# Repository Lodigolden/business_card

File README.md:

# Business Card

## Overview
I saw the idea for a PCB business card online, but for the most part the PCBs didn't actually do anything. I saw a fun opportunity to give anyone who's got the card a clock/thermometer that they might get some use out of.

## Use

## Build Your Own!
See the Bill of Materials (BoM) in the docs/ folder.

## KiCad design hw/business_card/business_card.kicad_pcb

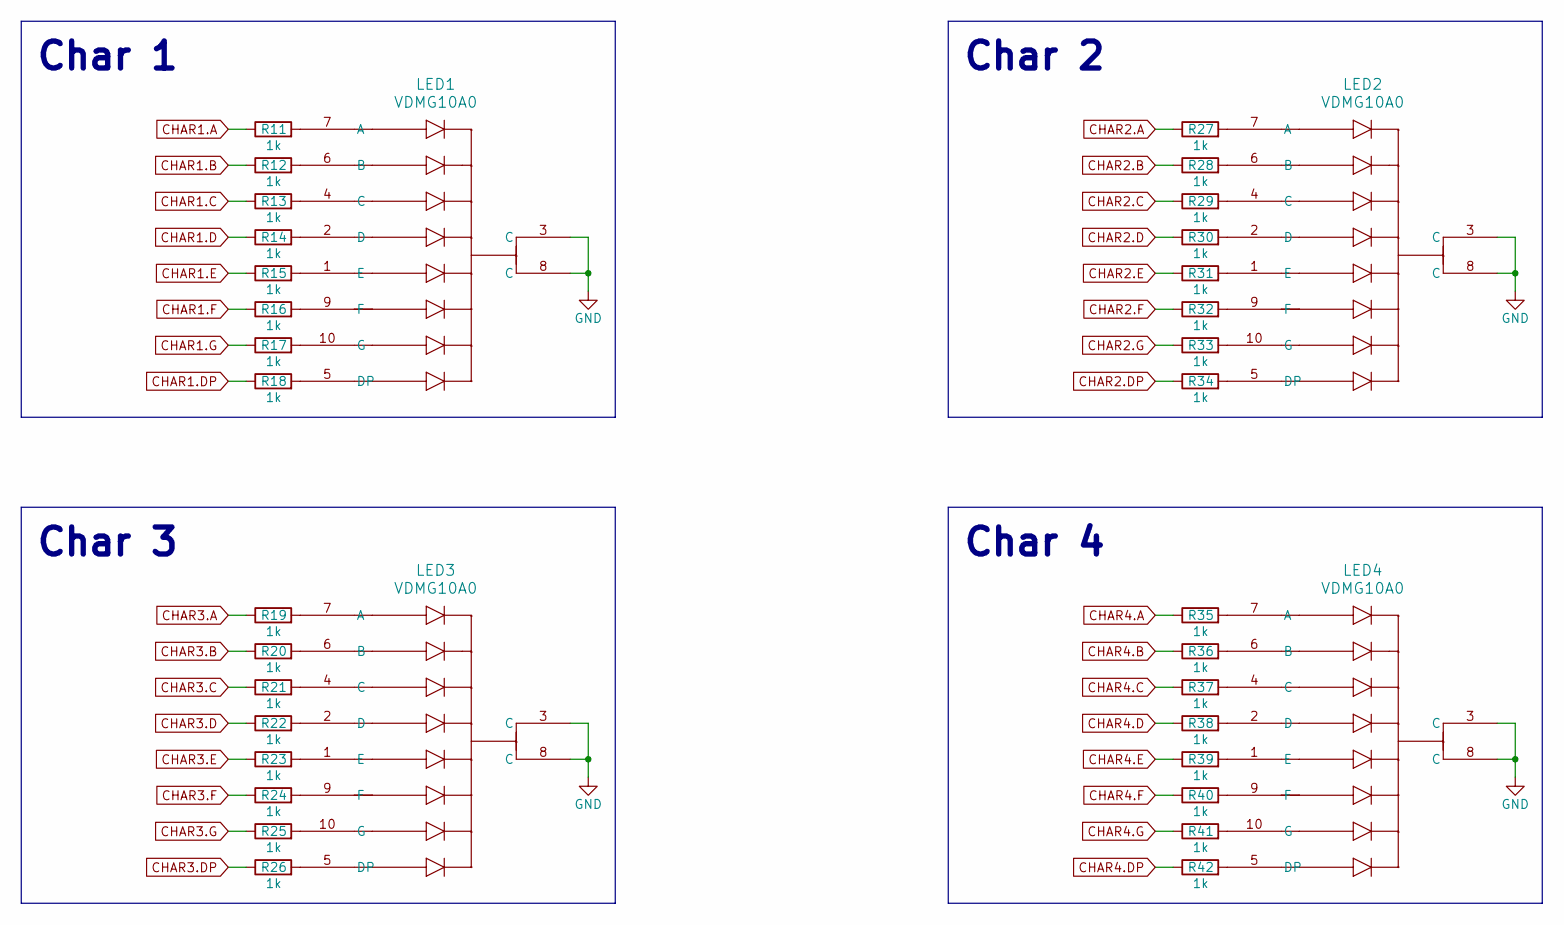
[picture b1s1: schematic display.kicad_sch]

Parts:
LED1, LED2, LED3, LED4: VDMG10A0; SMT_MG10A0_VIS
R11, R12, R13, R14, R15, R16, R17, R18, R19, R20, R21, R22, R23, R24, R25, R26, R27, R28, R29, R30, R31, R32, R33, R34, R35, R36, R37, R38, R39, R40, R41, R42: 1k; R_0402_1005Metric

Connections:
CHAR1.A: R11.1; also elsewhere on the board
CHAR1.B: R12.1; also elsewhere on the board
CHAR1.C: R13.1; also elsewhere on the board
CHAR1.D: R14.1; also elsewhere on the board
CHAR1.DP: R18.1; also elsewhere on the board
CHAR1.E: R15.1; also elsewhere on the board
CHAR1.F: R16.1; also elsewhere on the board
CHAR1.G: R17.1; also elsewhere on the board
CHAR2.A: R27.1; also elsewhere on the board
CHAR2.B: R28.1; also elsewhere on the board
CHAR2.C: R29.1; also elsewhere on the board
CHAR2.D: R30.1; also elsewhere on the board
CHAR2.DP: R34.1; also elsewhere on the board
CHAR2.E: R31.1; also elsewhere on the board
CHAR2.F: R32.1; also elsewhere on the board
CHAR2.G: R33.1; also elsewhere on the board
CHAR3.A: R19.1; also elsewhere on the board
CHAR3.B: R20.1; also elsewhere on the board
CHAR3.C: R21.1; also elsewhere on the board
CHAR3.D: R22.1; also elsewhere on the board
CHAR3.DP: R26.1; also elsewhere on the board
CHAR3.E: R23.1; also elsewhere on the board
CHAR3.F: R24.1; also elsewhere on the board
CHAR3.G: R25.1; also elsewhere on the board
CHAR4.A: R35.1; also elsewhere on the board
CHAR4.B: R36.1; also elsewhere on the board
CHAR4.C: R37.1; also elsewhere on the board
CHAR4.D: R38.1; also elsewhere on the board
CHAR4.DP: R42.1; also elsewhere on the board
CHAR4.E: R39.1; also elsewhere on the board
CHAR4.F: R40.1; also elsewhere on the board
CHAR4.G: R41.1; also elsewhere on the board
GND: LED1.3 (C), LED1.8 (C), LED2.3 (C), LED2.8 (C), LED3.3 (C), LED3.8 (C), LED4.3 (C), LED4.8 (C); also elsewhere on the board
unnamed: LED1.7 (A), R11.2
unnamed: LED1.6 (B), R12.2
unnamed: LED1.4 (C), R13.2
unnamed: LED1.2 (D), R14.2
unnamed: LED1.5 (DP), R18.2
unnamed: LED1.1 (E), R15.2
unnamed: LED1.9 (F), R16.2
unnamed: LED1.10 (G), R17.2
unnamed: LED2.7 (A), R27.2
unnamed: LED2.6 (B), R28.2
unnamed: LED2.4 (C), R29.2
unnamed: LED2.2 (D), R30.2
unnamed: LED2.5 (DP), R34.2
unnamed: LED2.1 (E), R31.2
unnamed: LED2.9 (F), R32.2
unnamed: LED2.10 (G), R33.2
unnamed: LED3.7 (A), R19.2
unnamed: LED3.6 (B), R20.2
unnamed: LED3.4 (C), R21.2
unnamed: LED3.2 (D), R22.2
unnamed: LED3.5 (DP), R26.2
unnamed: LED3.1 (E), R23.2
unnamed: LED3.9 (F), R24.2
unnamed: LED3.10 (G), R25.2
unnamed: LED4.7 (A), R35.2
unnamed: LED4.6 (B), R36.2
unnamed: LED4.4 (C), R37.2
unnamed: LED4.2 (D), R38.2
unnamed: LED4.5 (DP), R42.2
unnamed: LED4.1 (E), R39.2
unnamed: LED4.9 (F), R40.2
unnamed: LED4.10 (G), R41.2

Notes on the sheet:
Char 3
Char 4
Char 2
Char 1

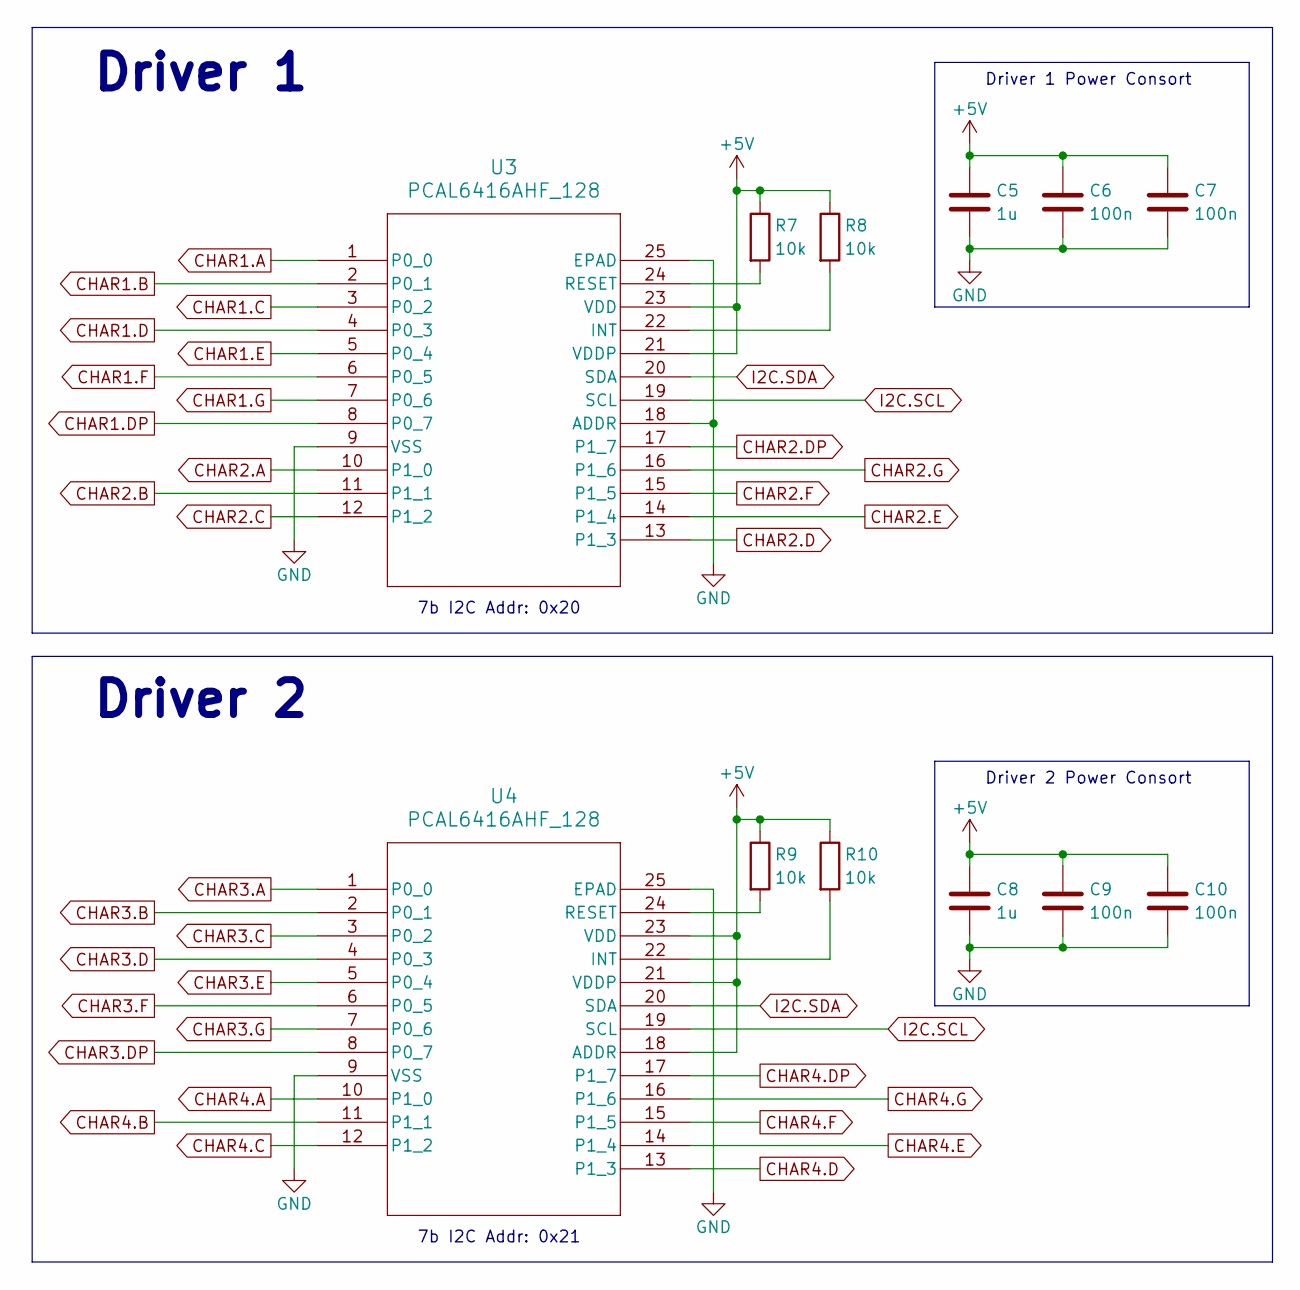
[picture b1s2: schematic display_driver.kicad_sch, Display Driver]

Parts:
C5, C8: 1u; C_0603_1608Metric
C6, C7, C9, C10: 100n; C_0402_1005Metric
R7, R8, R9, R10: 10k; R_0402_1005Metric
U3, U4: PCAL6416AHF_128; HWQFN24_PCAL_NXP

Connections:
+5V: C5.1, C6.1, C7.1, C8.1, C9.1, C10.1, R7.1, R8.1, R9.1, R10.1, U3.21 (VDDP), U3.23 (VDD), U4.18 (ADDR), U4.21 (VDDP), U4.23 (VDD); also elsewhere on the board
CHAR1.A: U3.1 (P0_0); also elsewhere on the board
CHAR1.B: U3.2 (P0_1); also elsewhere on the board
CHAR1.C: U3.3 (P0_2); also elsewhere on the board
CHAR1.D: U3.4 (P0_3); also elsewhere on the board
CHAR1.DP: U3.8 (P0_7); also elsewhere on the board
CHAR1.E: U3.5 (P0_4); also elsewhere on the board
CHAR1.F: U3.6 (P0_5); also elsewhere on the board
CHAR1.G: U3.7 (P0_6); also elsewhere on the board
CHAR2.A: U3.10 (P1_0); also elsewhere on the board
CHAR2.B: U3.11 (P1_1); also elsewhere on the board
CHAR2.C: U3.12 (P1_2); also elsewhere on the board
CHAR2.D: U3.13 (P1_3); also elsewhere on the board
CHAR2.DP: U3.17 (P1_7); also elsewhere on the board
CHAR2.E: U3.14 (P1_4); also elsewhere on the board
CHAR2.F: U3.15 (P1_5); also elsewhere on the board
CHAR2.G: U3.16 (P1_6); also elsewhere on the board
CHAR3.A: U4.1 (P0_0); also elsewhere on the board
CHAR3.B: U4.2 (P0_1); also elsewhere on the board
CHAR3.C: U4.3 (P0_2); also elsewhere on the board
CHAR3.D: U4.4 (P0_3); also elsewhere on the board
CHAR3.DP: U4.8 (P0_7); also elsewhere on the board
CHAR3.E: U4.5 (P0_4); also elsewhere on the board
CHAR3.F: U4.6 (P0_5); also elsewhere on the board
CHAR3.G: U4.7 (P0_6); also elsewhere on the board
CHAR4.A: U4.10 (P1_0); also elsewhere on the board
CHAR4.B: U4.11 (P1_1); also elsewhere on the board
CHAR4.C: U4.12 (P1_2); also elsewhere on the board
CHAR4.D: U4.13 (P1_3); also elsewhere on the board
CHAR4.DP: U4.17 (P1_7); also elsewhere on the board
CHAR4.E: U4.14 (P1_4); also elsewhere on the board
CHAR4.F: U4.15 (P1_5); also elsewhere on the board
CHAR4.G: U4.16 (P1_6); also elsewhere on the board
GND: C5.2, C6.2, C7.2, C8.2, C9.2, C10.2, U3.9 (VSS), U3.18 (ADDR), U3.25 (EPAD), U4.9 (VSS), U4.25 (EPAD); also elsewhere on the board
I2C.SCL: U3.19 (SCL), U4.19 (SCL); also elsewhere on the board
I2C.SDA: U3.20 (SDA), U4.20 (SDA); also elsewhere on the board
unnamed: R8.2, U3.22 (INT)
unnamed: R7.2, U3.24 (RESET)
unnamed: R10.2, U4.22 (INT)
unnamed: R9.2, U4.24 (RESET)

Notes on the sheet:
Driver 2 Power Consort
Driver 2
Driver 1 Power Consort
7b I2C Addr: 0x21
Driver 1
7b I2C Addr: 0x20

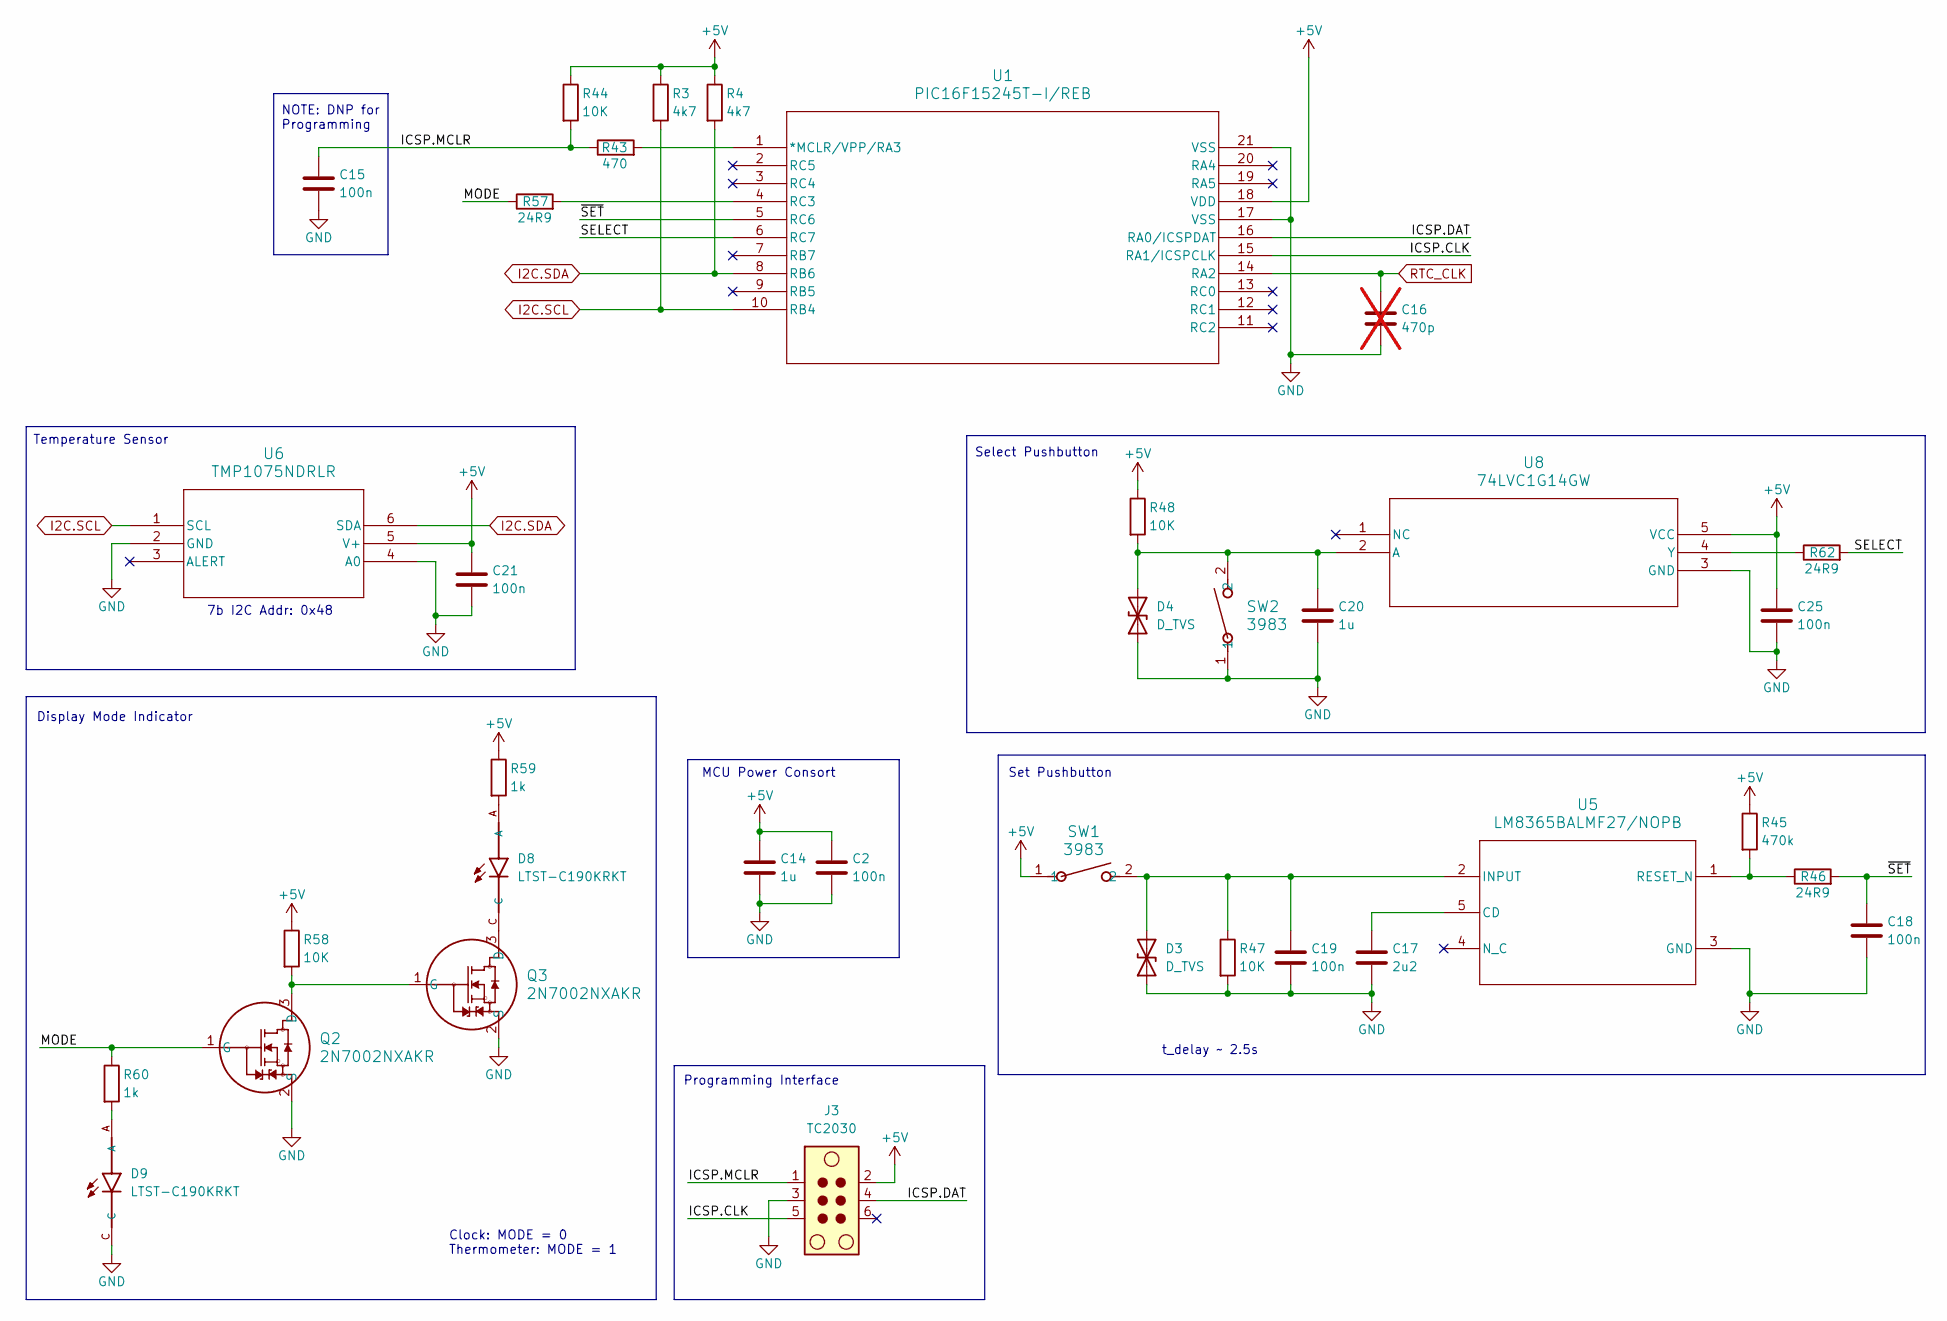
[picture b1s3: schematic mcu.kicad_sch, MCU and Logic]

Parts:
C2, C15, C18, C19, C21, C25: 100n; C_0402_1005Metric
C14, C20: 1u; C_0603_1608Metric
C16: 470p; C_0402_1005Metric; not fitted
C17: 2u2; C_0603_1608Metric
D3, D4: D_TVS; D_SOD-523
D8, D9: LTST-C190KRKT; LEDC1608X35N
J3: TC2030; Tag-Connect_TC2030-IDC-FP_2x03_P1.27mm_Vertical
Q2, Q3: 2N7002NXAKR; TO-236AB_SOT23_NEX
R3, R4: 4k7; R_0402_1005Metric
R43: 470; R_0402_1005Metric
R44, R47, R48, R58: 10K; R_0402_1005Metric
R45: 470k; R_0402_1005Metric
R46, R57, R62: 24R9; R_0402_1005Metric
R59, R60: 1k; R_0402_1005Metric
SW1, SW2: 3983; SW_3983_ADA
U1: PIC16F15245T-I/REB; VQFN20_REB_MCH
U5: LM8365BALMF27/NOPB; DBV0005A_L
U6: TMP1075NDRLR; SOT5X3-6_DRL_TEX
U8: 74LVC1G14GW; 74lvc1g14gw

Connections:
+5V: C2.1, C14.1, C21.1, C25.1, J3.2, R3.1, R4.1, R44.1, R45.1, R48.1, R58.1, R59.1, SW1.1, U1.18 (VDD), U6.5 (V+), U8.5 (VCC); also elsewhere on the board
/MCU/ICSP.CLK: J3.5, U1.15 (RA1/ICSPCLK)
/MCU/ICSP.DAT: J3.4, U1.16 (RA0/ICSPDAT)
/MCU/ICSP.MCLR: C15.1, J3.1, R43.1, R44.2
/MCU/MODE: Q2.1 (G), R57.1, R60.1
/MCU/SELECT: R62.2, U1.6 (RC7)
/MCU/~SET: C18.1, R46.2, U1.5 (RC6)
GND: C2.2, C14.2, C15.2, C16.2, C17.2, C18.2, C19.2, C20.2, C21.2, C25.2, D3.1 (A1), D4.1 (A1), D9.C, J3.3, Q2.2 (S), Q3.2 (S), R47.2, SW2.1, U1.17 (VSS), U1.21 (VSS), U5.3 (GND), U6.2 (GND), U6.4 (A0), U8.3 (GND); also elsewhere on the board
I2C.SCL: R3.2, U1.10 (RB4), U6.1 (SCL); also elsewhere on the board
I2C.SDA: R4.2, U1.8 (RB6), U6.6 (SDA); also elsewhere on the board
unnamed: C19.1, D3.2 (A2), R47.1, SW1.2, U5.2 (INPUT)
unnamed: C20.1, D4.2 (A2), R48.2, SW2.2, U8.2 (A)
unnamed: D8.A, R59.2
unnamed: D9.A, R60.2
unnamed: Q2.3 (D), Q3.1 (G), R58.2
unnamed: D8.C, Q3.3 (D)
unnamed: R43.2, U1.1 (*MCLR/VPP/RA3)
unnamed: R57.2, U1.4 (RC3)
unnamed: C17.1, U5.5 (CD)
unnamed: R45.2, R46.1, U5.1 (RESET_N)
unnamed: R62.1, U8.4 (Y)
RTC_CLK: C16.1, U1.14 (RA2); also elsewhere on the board

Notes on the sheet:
Temperature Sensor
Display Mode Indicator
NOTE: DNP for Programming
7b I2C Addr: 0x48
MCU Power Consort
Programming Interface
Select Pushbutton
Set Pushbutton
t_delay ~ 2.5s
Clock: MODE = 0 Thermometer: MODE = 1

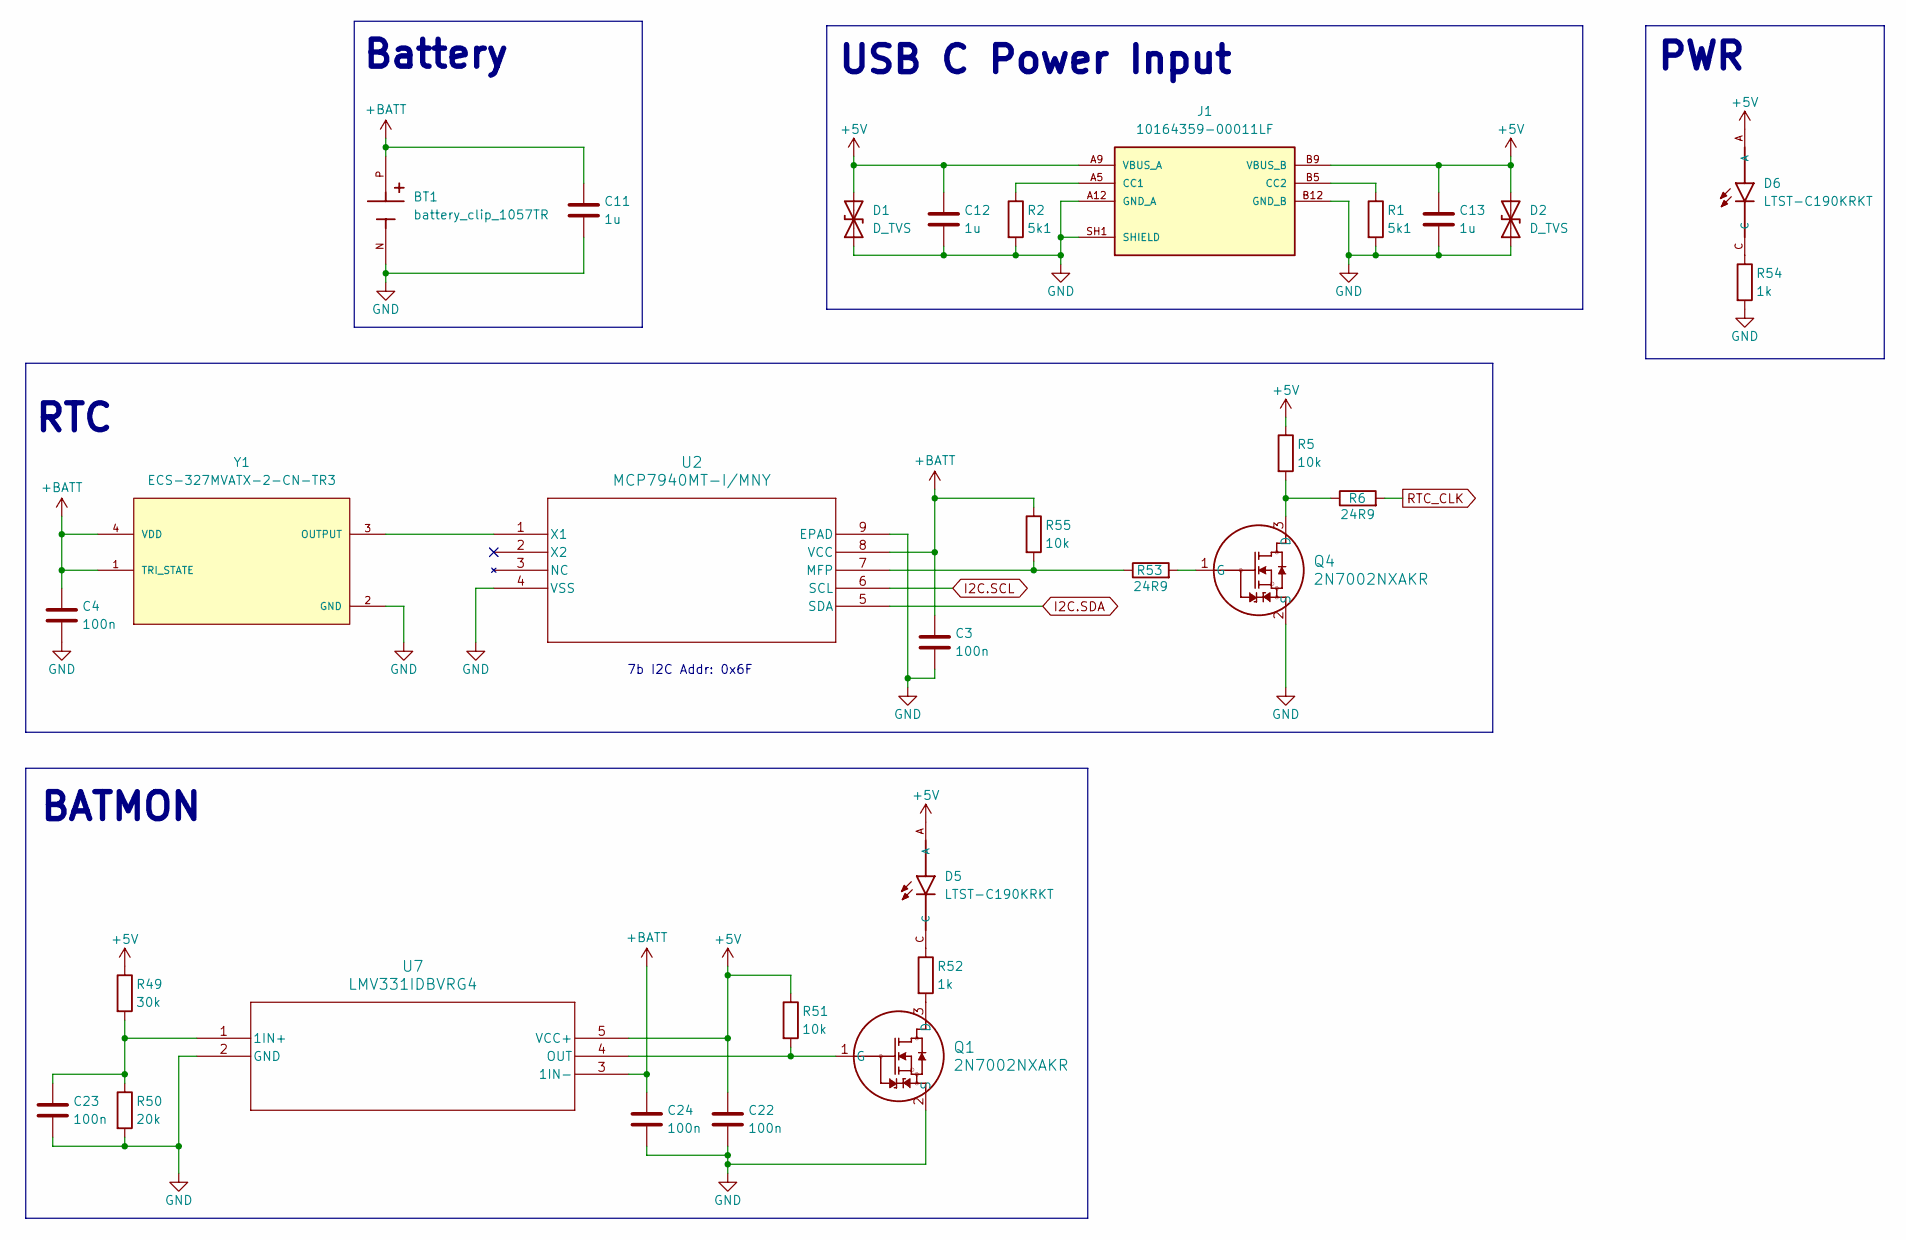
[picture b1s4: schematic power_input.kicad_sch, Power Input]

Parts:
BT1: battery_clip_1057TR; BAT_1057TR; PARTREV H
C3, C4, C22, C23, C24: 100n; C_0402_1005Metric
C11, C12, C13: 1u; C_0603_1608Metric
D1, D2: D_TVS; D_SOD-523
D5, D6: LTST-C190KRKT; LEDC1608X35N
J1: 10164359-00011LF; AMPHENOL_10164359-00011LF; PARTREV A
Q1, Q4: 2N7002NXAKR; TO-236AB_SOT23_NEX
R1, R2: 5k1; R_0402_1005Metric
R5, R51, R55: 10k; R_0402_1005Metric
R6, R53: 24R9; R_0402_1005Metric
R49: 30k; R_0402_1005Metric
R50: 20k; R_0402_1005Metric
R52, R54: 1k; R_0402_1005Metric
U2: MCP7940MT-I/MNY; TDFN8_2x3MC_MCH
U7: LMV331IDBVRG4; DBV5
Y1: ECS-327MVATX-2-CN-TR3; OSC_ECS-2520S25-250-FN-TR; PARTREV 2017

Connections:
+5V: C12.1, C13.1, C22.1, D1.2 (A2), D2.2 (A2), D5.A, D6.A, J1.A9 (VBUS_A), J1.B9 (VBUS_B), R5.1, R49.1, R51.1, U7.5 (VCC+); also elsewhere on the board
+BATT: BT1.P, C3.1, C4.1, C11.1, C24.1, R55.1, U2.8 (VCC), U7.3 (1IN-), Y1.1 (TRI_STATE), Y1.4 (VDD)
GND: BT1.N, C3.2, C4.2, C11.2, C12.2, C13.2, C22.2, C23.2, C24.2, D1.1 (A1), D2.1 (A1), J1.A12 (GND_A), J1.B12 (GND_B), J1.SH1 (SHIELD), J1.SH2 (SHIELD), J1.SH3 (SHIELD), J1.SH4 (SHIELD), Q1.2 (S), Q4.2 (S), R1.2, R2.2, R50.2, R54.2, U2.4 (VSS), U2.9 (EPAD), U7.2 (GND), Y1.2 (GND); also elsewhere on the board
I2C.SCL: U2.6 (SCL); also elsewhere on the board
I2C.SDA: U2.5 (SDA); also elsewhere on the board
unnamed: D5.C, R52.1
unnamed: D6.C, R54.1
unnamed: J1.A5 (CC1), R2.1
unnamed: J1.B5 (CC2), R1.1
unnamed: Q1.3 (D), R52.2
unnamed: Q1.1 (G), R51.2, U7.4 (OUT)
unnamed: Q4.3 (D), R5.2, R6.1
unnamed: Q4.1 (G), R53.2
unnamed: R53.1, R55.2, U2.7 (MFP)
unnamed: U2.1 (X1), Y1.3 (OUTPUT)
unnamed: C23.1, R49.2, R50.1, U7.1 (1IN+)
RTC_CLK: R6.2; also elsewhere on the board

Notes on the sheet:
RTC
USB C Power Input
7b I2C Addr: 0x6F
Battery
PWR
BATMON

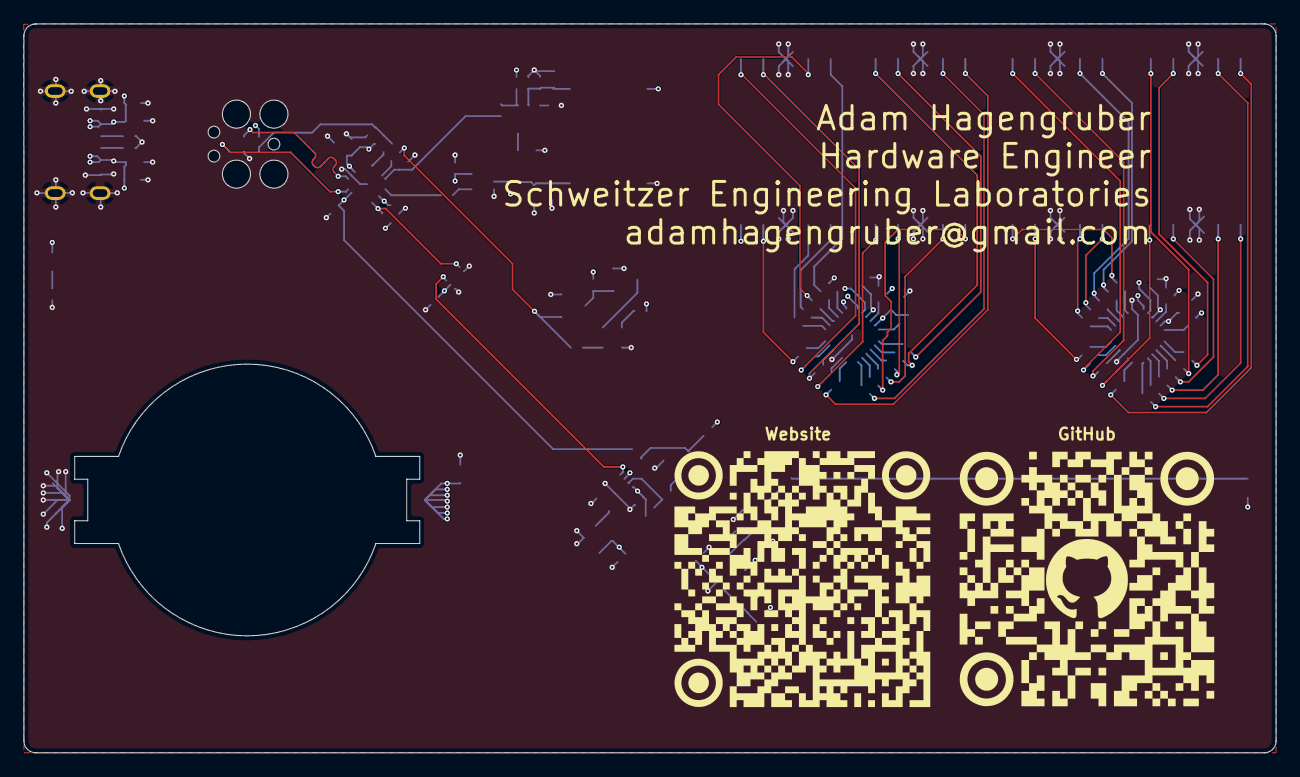
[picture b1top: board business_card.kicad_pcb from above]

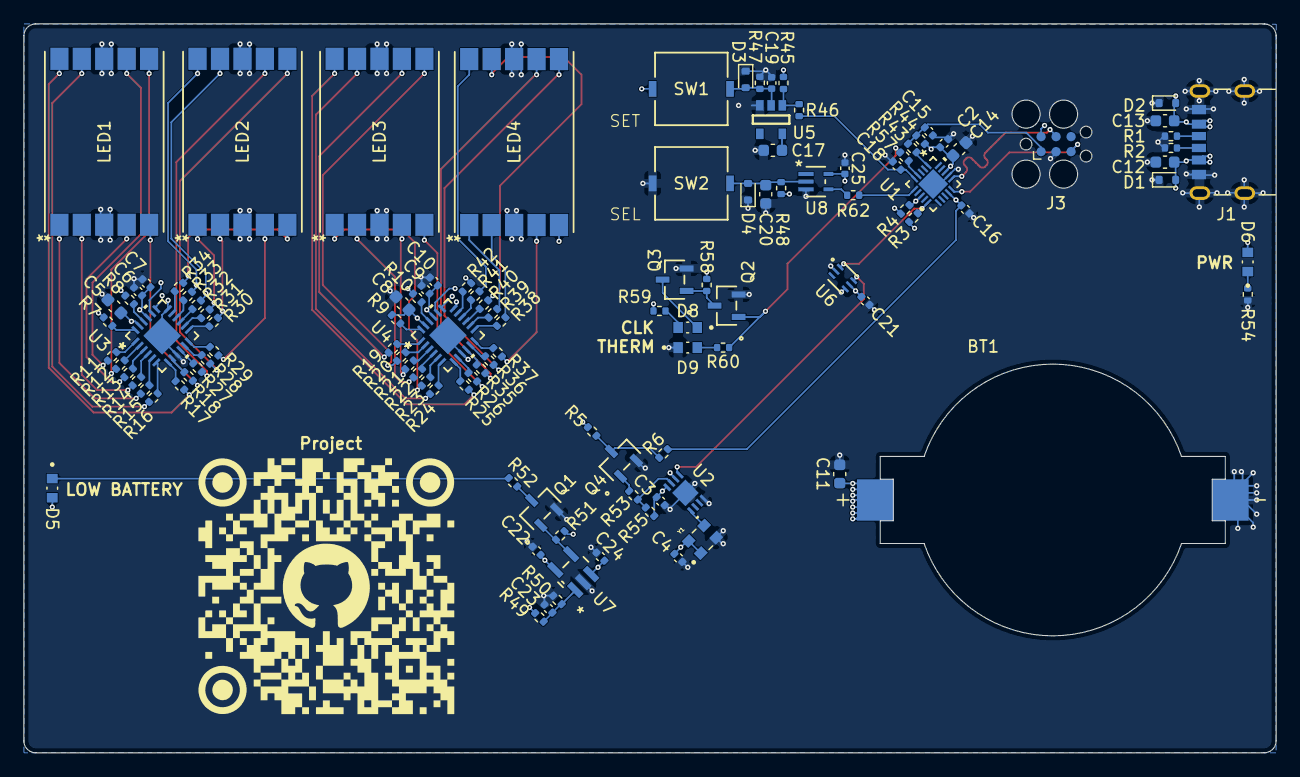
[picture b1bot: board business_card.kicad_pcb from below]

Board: 4 copper layers, 106.0 x 61.7 mm, 114 parts (114 on the bottom side), 102 nets.
